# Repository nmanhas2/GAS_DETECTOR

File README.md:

# GAS_DETECTOR
Gas Detection project I made while attending NAIT

This includes the PCB and circuit design I made using KiCad EDA. 

Here's how it works:

-Using a gas sensor to detect smoke/gas in PPM (parts per million, standard for measuring the volume of a gas)

-Once the sensor detects a certain amount of gas (displayed on an I2C supported LCD), an “alarm” activates (piezo buzzer). The volume of gas is not accurate I believe, as I had problems with determining the calculations

-The LCD will display the current volume of gas detected by the gas sensor in PPM

-Push button for Reset

Involves the following components:

-MQ-2 gas sensor, widely used with lots of resources/examples to look at, works at 5V (https://components101.com/sensors/mq2-gas-sensor) https://media.digikey.com/pdf/Data%20Sheets/Seeed%20Technology/101020055_Web.pdf

-LCD w/ I2C: AMC0802BR-B-Y6WFDY-I2C (https://www.digikey.ca/en/products/detail/orient-display/AMC0802BR-B-Y6WFDY-I2C/12089323), cheap on digikey, runs at 5V as well. 0111110 = I2C address 

-BH9VPC 9V battery holder (had this on hand) + LM7805 linear voltage regulator to get the 5V needed for everything

-ATmega328P for the microcontroller https://ww1.microchip.com/downloads/en/DeviceDoc/Atmel-7810-Automotive-Microcontrollers-ATmega328P_Datasheet.pdf

-Piezo Buzzer for the alarm (PS1240P02BT) https://www.digikey.ca/en/products/detail/tdk-corporation/PS1240P02BT/935924, can run on 3V minimum up to a maximum of 30Vp

-A push button

Here is the circuit schematic (may be difficult to see):

Here is the PCB design:

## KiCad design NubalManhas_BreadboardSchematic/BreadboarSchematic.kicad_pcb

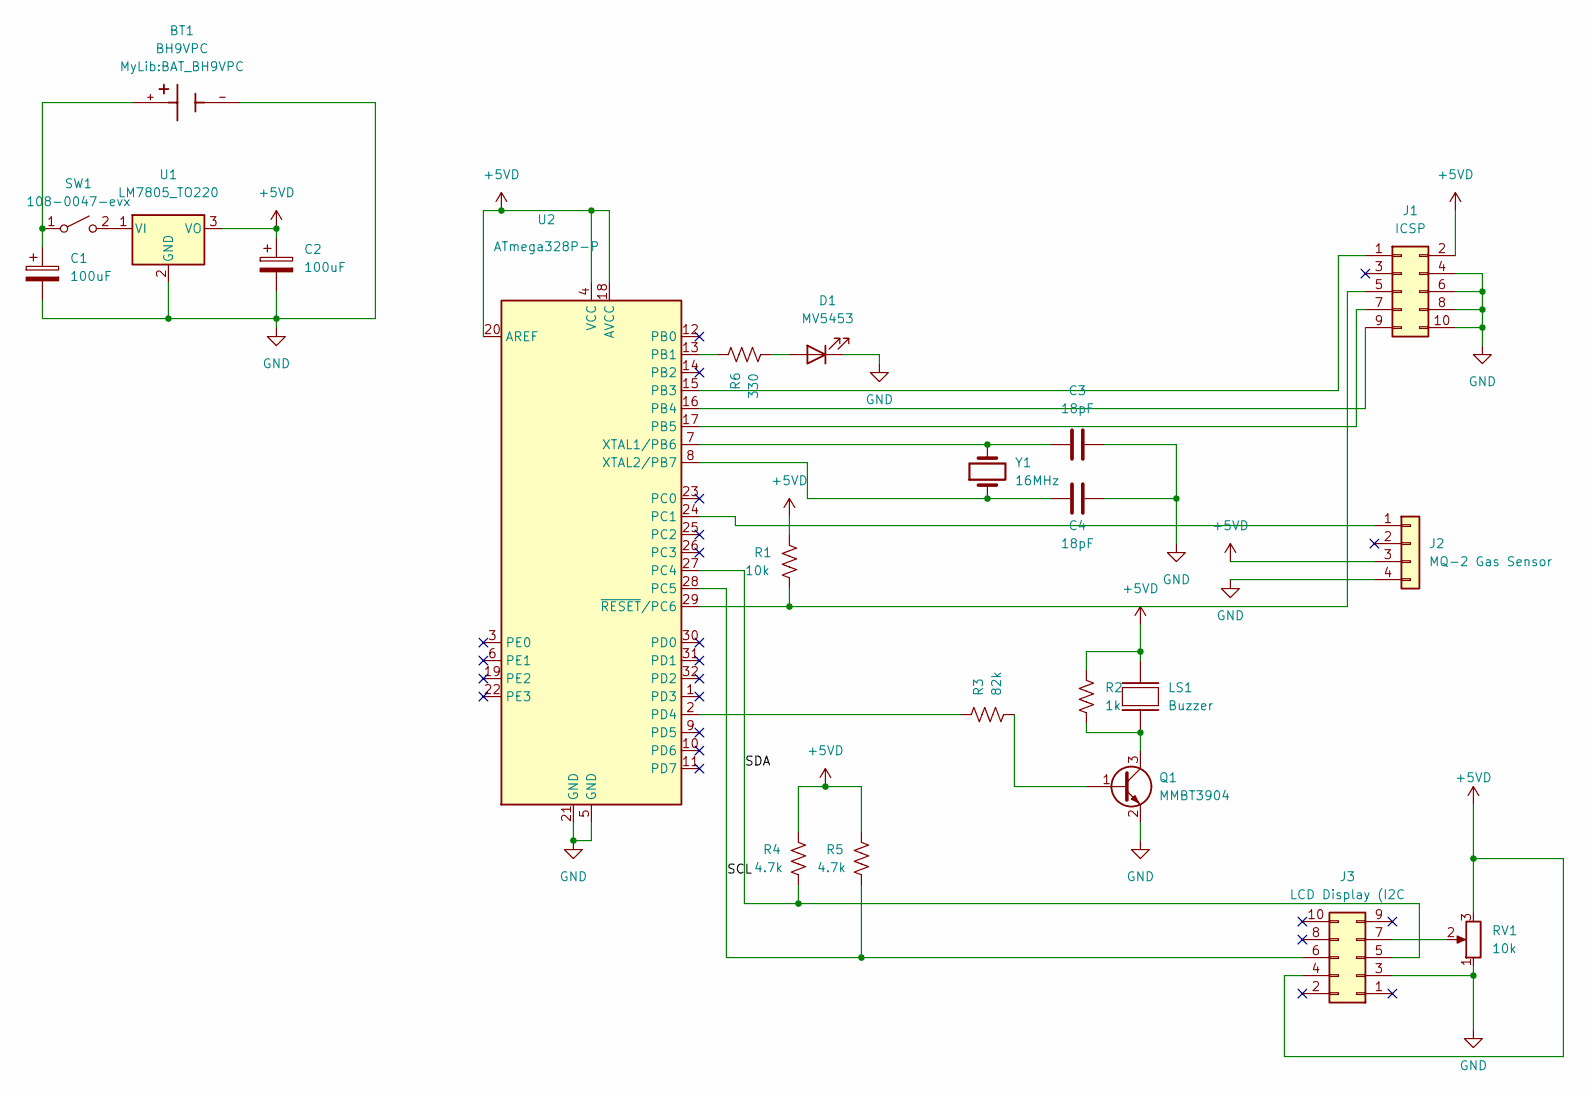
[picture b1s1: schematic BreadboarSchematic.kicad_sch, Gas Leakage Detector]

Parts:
BT1: BH9VPC; BAT_BH9VPC; PARTREV F
C1, C2: 100uF; CP_Elec_6.3x5.8
C3, C4: 18pF; C_1206_3216Metric
D1: MV5453; RESC3015X65
J1: ICSP; PinSocket_2x05_P2.54mm_Vertical
J2: MQ-2 Gas Sensor; PinHeader_1x04_P2.54mm_Vertical
J3: LCD Display (I2C; PinHeader_2x05_P2.54mm_Vertical
LS1: Buzzer; XDCR_PS1240P02BT
Q1: MMBT3904; SOT-23
R1: 10k; R_1206_3216Metric
R2: 1k; R_1206_3216Metric
R3: 82k; R_1206_3216Metric
R4, R5: 4.7k; R_1206_3216Metric
R6: 330; R_1206_3216Metric
RV1: 10k; Potentiometer_Bourns_3296W_Vertical
SW1: 108-0047-evx; 1080047EVX
U1: LM7805_TO220; TO-220-3_Vertical
U2: ATmega328P-P; TQFP-32_7x7mm_P0.8mm
Y1: 16MHz; Crystal_SMD_ECS_CSM3X-2Pin_7.6x4.1mm

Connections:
+5VD: C2.1, J1.2, J2.3, J3.4, LS1.2, R1.1, R2.1, R4.1, R5.1, RV1.3, U1.3 (VO), U2.4 (VCC), U2.18 (AVCC), U2.20 (AREF)
/SCL: J3.6, R5.2, U2.28 (PC5)
/SDA: J3.5, R4.2, U2.27 (PC4)
GND: BT1.-, C1.2, C2.2, C3.2, C4.2, D1.1 (K), J1.4, J1.6, J1.8, J1.10, J2.4, J3.3, Q1.2 (E), RV1.1, U1.2 (GND), U2.5 (GND), U2.21 (GND)
unnamed: BT1.+, C1.1, SW1.1 (A)
unnamed: C3.1, U2.7 (XTAL1/PB6), Y1.2
unnamed: C4.1, U2.8 (XTAL2/PB7), Y1.1
unnamed: D1.2 (A), R6.2
unnamed: J1.1, U2.15 (PB3)
unnamed: J1.5, R1.2, U2.29 (~RESET/PC6)
unnamed: J1.7, U2.17 (PB5)
unnamed: J1.9, U2.16 (PB4)
unnamed: J2.1, U2.24 (PC1)
unnamed: J3.7, RV1.2
unnamed: LS1.1, Q1.3 (C), R2.2
unnamed: Q1.1 (B), R3.2
unnamed: R3.1, U2.2 (PD4)
unnamed: R6.1, U2.13 (PB1)
unnamed: SW1.2 (B), U1.1 (VI)

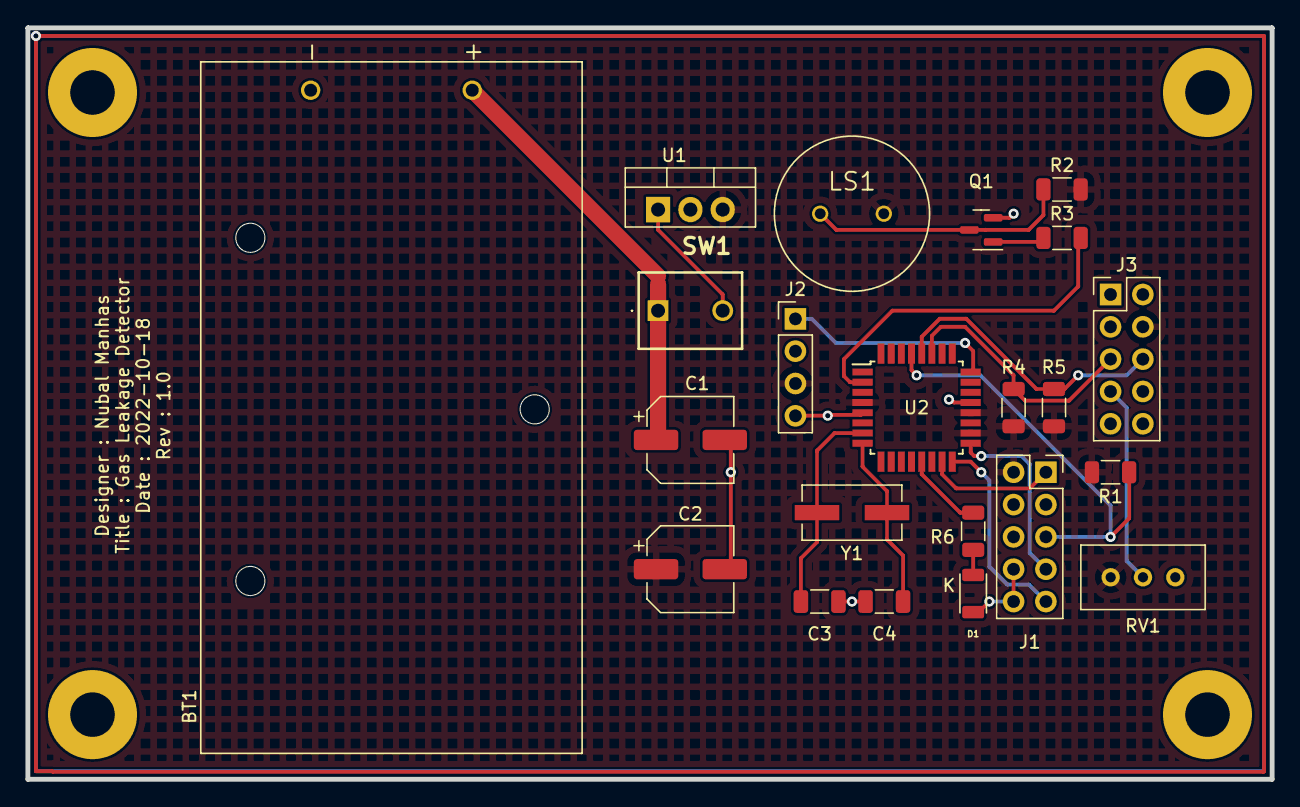
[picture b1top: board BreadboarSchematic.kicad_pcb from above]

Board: 2 copper layers, 97.8 x 59.1 mm, 22 parts (0 on the bottom side), 19 nets.

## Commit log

2024-01-20 Uploaded KiCad Design
2024-01-20 Uploaded code
2024-01-21 Added KiCad design
